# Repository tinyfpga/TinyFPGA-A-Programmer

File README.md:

# TinyFPGA Programmer
The TinyFPGA Programmer is a very simple USB-JTAG bridge designed to 
program bitstreams onto TinyFPGA A1 and A2 boards.  

## Serial Protocol
The programmer firmware appears as a generic USB serial port when you connect it
to a computer.  Control of the GPIO pins on the programmer is through this simple
serial interface.  

### Command Format
Commands are encoded as 8-bit bytes with a command type field and data payload.
The payload is typically a 6-bit bitmap representing the GPIO pins of the programmer.

|      7:6     | 5 | 4 | 3 | 2 | 1 | 0 |
|--------------|---|---|---|---|---|---|
| Command Type |TMS|TCK|TDI|TDO|RC1|RC0|

### Commands

|Opcode |             Command           |
|-------|-------------------------------|
|   0   | Configure Input/Output        |
|   1   | Extended Command (Unused)     |
|   2   | Set Outputs                   |
|   3   | Set Outputs and Sample Inputs |

#### Configure Input/Output
For each of the GPIO pins, set the direction of the pin.  
* 1: Set GPIO pin n to INPUT
* 0: Set GPIO pin n to OUTPUT

#### Extended Command
Reserved for future command expansion.

#### Set Outputs
Set each of the output pins to the given values.

#### Set Outputs and Sample Inputs
Set each of the output pins to the given values and return a byte representing
the current values of the input pins.  

### General Usage
For serial interfaces like JTAG this protocol divides the maximum possible bandwidth
by 8 from the USB to JTAG interface.  This means we might get 0.5MHz JTAG programming speed.
That speed is actually fast enough to transfer all the data to the FPGA in a few seconds.  However
the configuration flash on the FPGA actually needs a fair bit of time after erase and write operations
that will slow down the programming operatuon.

What can really slow down programming is the turnaround time for reading back data from the FPGA.  
For the most part data is going in one direction from the host computer to the programmer to the FPGA.  
For these cases we can  use the `Set Outputs` command and not wait for any data to return.  However 
there are times when we may  need to poll a status bit to see if the FPGA has finished an erase or 
write operation.  In this cases we will want to also sample the inputs and check the status.  These 
should not be timing sensitive because the FPGA is already busy.

Verifying the configuration data on the other hand could take a long time if not done carefully.  The
application talking to the programmer should make sure to write as many commands as it can before attempting
to read back the data from the serial interface.  Rather than paying a penalty for the turnaround time on
every read bit, we pay for it after reading dozens of bytes.  This should allow read-back of the configuration
data to be relatively quick and painless.

## Status
The project is currently in progress.  Initial schematic and PCBs have
been designed along with firmware for the USB microcontroller.  The PCBs
have been received from OSH Park and programmed with the firwmware.

The biggest task left is still developing the Python libraries for interfacing 
with the firmware and driving the JTAG interface and is currently in progress.

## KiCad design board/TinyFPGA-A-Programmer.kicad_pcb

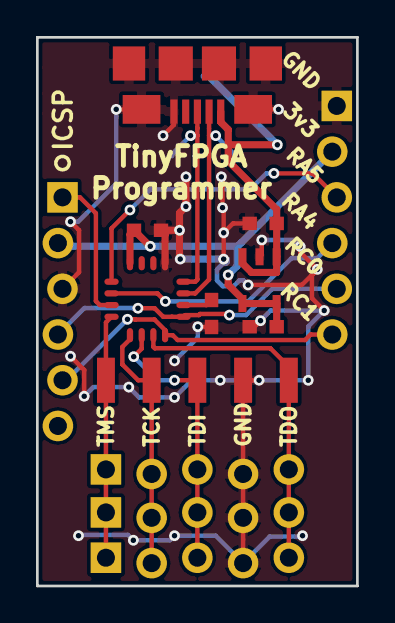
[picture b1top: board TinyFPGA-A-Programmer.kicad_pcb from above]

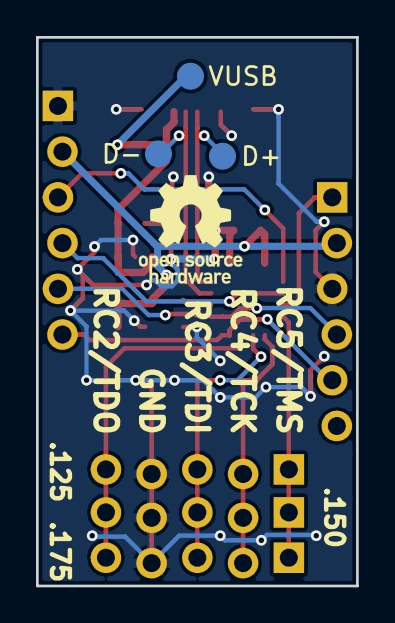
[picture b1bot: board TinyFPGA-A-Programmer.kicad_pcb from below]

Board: 2 copper layers, 17.8 x 30.5 mm, 16 parts (3 on the bottom side), 15 nets.

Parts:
C1, C2, C4: 1uF; C_0603
C3: 100nF; C_0603
D+: TEST; Measurement_Point_Round-SMD-Pad_Small
D-: TEST; Measurement_Point_Round-SMD-Pad_Small
J1: USB; FCI-Micro-USB
J2: JTAG; Pin_Header_Straight_1x05_Pitch2.54mm_SMD
J2#2, J2#3, J2#4: JTAG; Pin_Header_Straight_1x05_Pitch2.54mm
J3: ICSP; Pin_Header_Straight_1x06_Pitch2.54mm
J4: CONN_01X06; Pin_Header_Straight_1x06_Pitch2.54mm
U1: PIC16F1455-QFN16; QFN-16-1EP_4x4mm_Pitch0.65mm
U2: MIC5504-3.3YM5-TR; SOT23
VUSB: TEST; Measurement_Point_Round-SMD-Pad_Small

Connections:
+3V3: C2.1, C3.1, J3.2, J4.2, U1.16, U2.4, U2.5
+5V: C1.1, J1.1, U2.1, U2.3, VUSB.1
GND: C1.2, C2.2, C3.2, C4.1, J1.5, J1.6, J2.4, J2#2.4, J2#3.4, J2#4.4, J3.3, J4.1, U1.13, U2.2
ICSPCLK: J3.5, J4.6, U1.8
ICSPDAT: J3.4, J4.5, U1.9
unnamed: C4.2, U1.10
unnamed: D-.1, J1.2, U1.11
unnamed: D+.1, J1.3, U1.12
unnamed: J2.1, J2#2.1, J2#3.1, J2#4.1, U1.4
unnamed: J2.2, J2#2.2, J2#3.2, J2#4.2, U1.5
unnamed: J2.3, J2#2.3, J2#3.3, J2#4.3, U1.6
unnamed: J2.5, J2#2.5, J2#3.5, J2#4.5, U1.7
RA4: J4.4, U1.2
RA5: J4.3, U1.1
VPP: J3.1, U1.3

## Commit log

2017-08-03 add the files to ignore first...
2017-08-03 add pic firmware
2017-08-05 added programmer schematic and pcb layout
2017-08-05 added README and LICENSE
2017-08-19 Update README.md
    fixed a typo
2017-08-30 updated firmware to read from TDO
2017-08-30 implemented read path of SVF player
2017-08-31 SVF parsing and programming now works
2017-09-01 updated CPU clock multiplier for firmware
2017-09-04 big changes to drastically speed up flash program times
2017-09-05 updated schematic and PCB
2017-09-09 firmware ready for production
2017-09-09 changed name of usb_gpio.py
2017-09-09 more sensible name for tinyfpgaa.py
2017-09-11 updated programmer module to support gui
2017-09-15 fix bug related to MacOS
2017-09-15 Update tinyfpgaa.py
    workaround for bug in firmware related to MacOS virtual serial port driver and zero length data packets.
2017-09-21 updates to improve stability on MacOS
2017-10-02 fixed bug with programming EBR initialization data
2017-10-07 production firmware, added schematic pdf
2017-10-12 fixed introduced bug where jed fiels without ebr now fail
2020-01-16 Update tinyfpgaa to Python 3 and add simple command-line programmer.
2020-03-10 Add support for writing .bit files.
2020-03-10 Fix typo in __init__.py.
2021-02-03 fix for py39 https://bugs.python.org/issue38916
2022-05-30 Support editable installs correctly.
